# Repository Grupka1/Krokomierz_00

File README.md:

# Krokomierz_00
Projekt IPZ kompaktowego krokomierza który może być wszczepiny pod skórę

Szacowana długość pracy:

Mikrokontroler 2,5mA
Akcelerometr 0,14mA
Moduł BT 8mA (przy łączeniu ok 30mA)
sumarycznie 8+2,5+0,14=10,64mA
Czas pracy baterii o pojemności 5000mAh - 328.95h (ok 13 dni)

https://biomedical-engineering-online.biomedcentral.com/articles/10.1186/1475-925X-13-79 - Praca naukowa (Pozyskiwanie energii dla wszczepialnych urządzeń biomedycznych).

[https://zadar.pl/medyczne] - Filamenty medyczne

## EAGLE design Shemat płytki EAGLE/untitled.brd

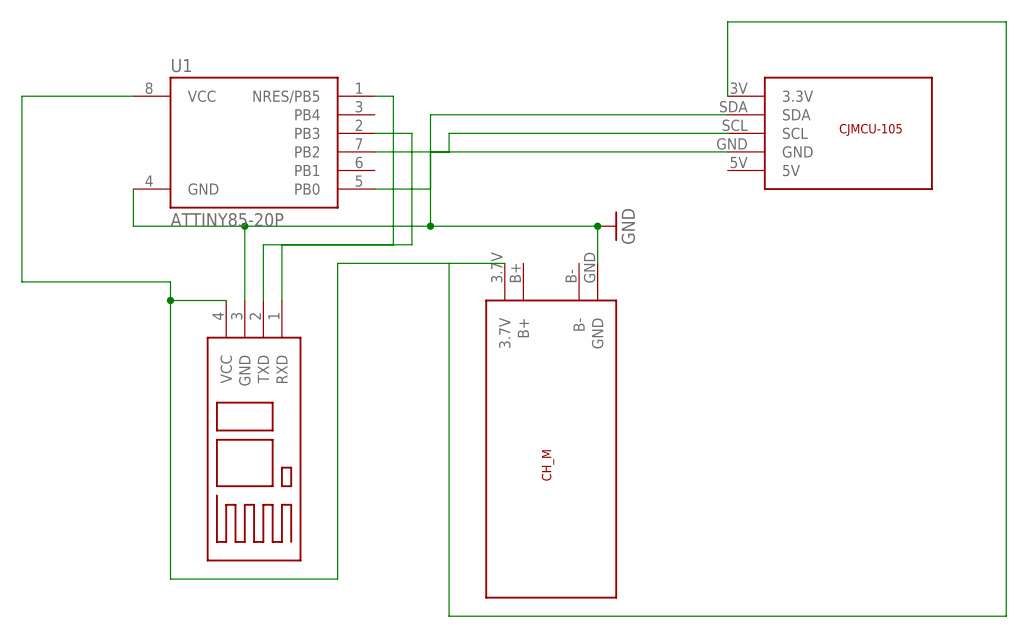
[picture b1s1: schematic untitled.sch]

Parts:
B1: BLUETOOTH
U1: ATTINY85-20P; PDIP08_300MIL
U$1: ADXLADXL; CJMCU-105
U$2: CH_MCH_M; CHARGING_MODULE

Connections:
GND: B1.3 (GND), U1.4 (GND), U$1.GND, U$2.GND
unnamed: B1.4 (VCC), U1.8 (VCC), U$1.3V (3.3V), U$2.3.7V
unnamed: B1.1 (RXD), U1.1 (NRES/PB5)
unnamed: B1.2 (TXD), U1.2 (PB3)
unnamed: U1.5 (PB0), U$1.SDA
unnamed: U1.7 (PB2), U$1.SCL

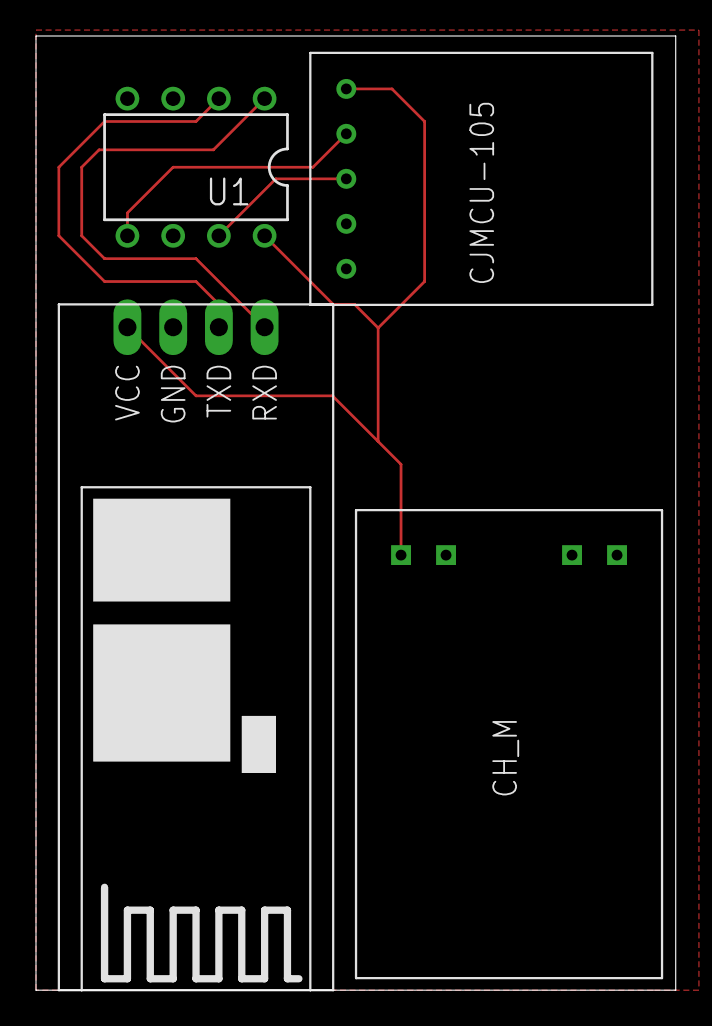
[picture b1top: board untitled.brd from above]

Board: 2 copper layers, 35.5 x 53.0 mm, 4 parts (0 on the bottom side), 6 nets.

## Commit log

2022-04-10 Krokomierz
    Krokomierz
2022-06-23 Schemat plytki EAGLE
2022-06-23 aplikacja 👍
2022-06-28 Video pracy
2022-06-28 Raport
